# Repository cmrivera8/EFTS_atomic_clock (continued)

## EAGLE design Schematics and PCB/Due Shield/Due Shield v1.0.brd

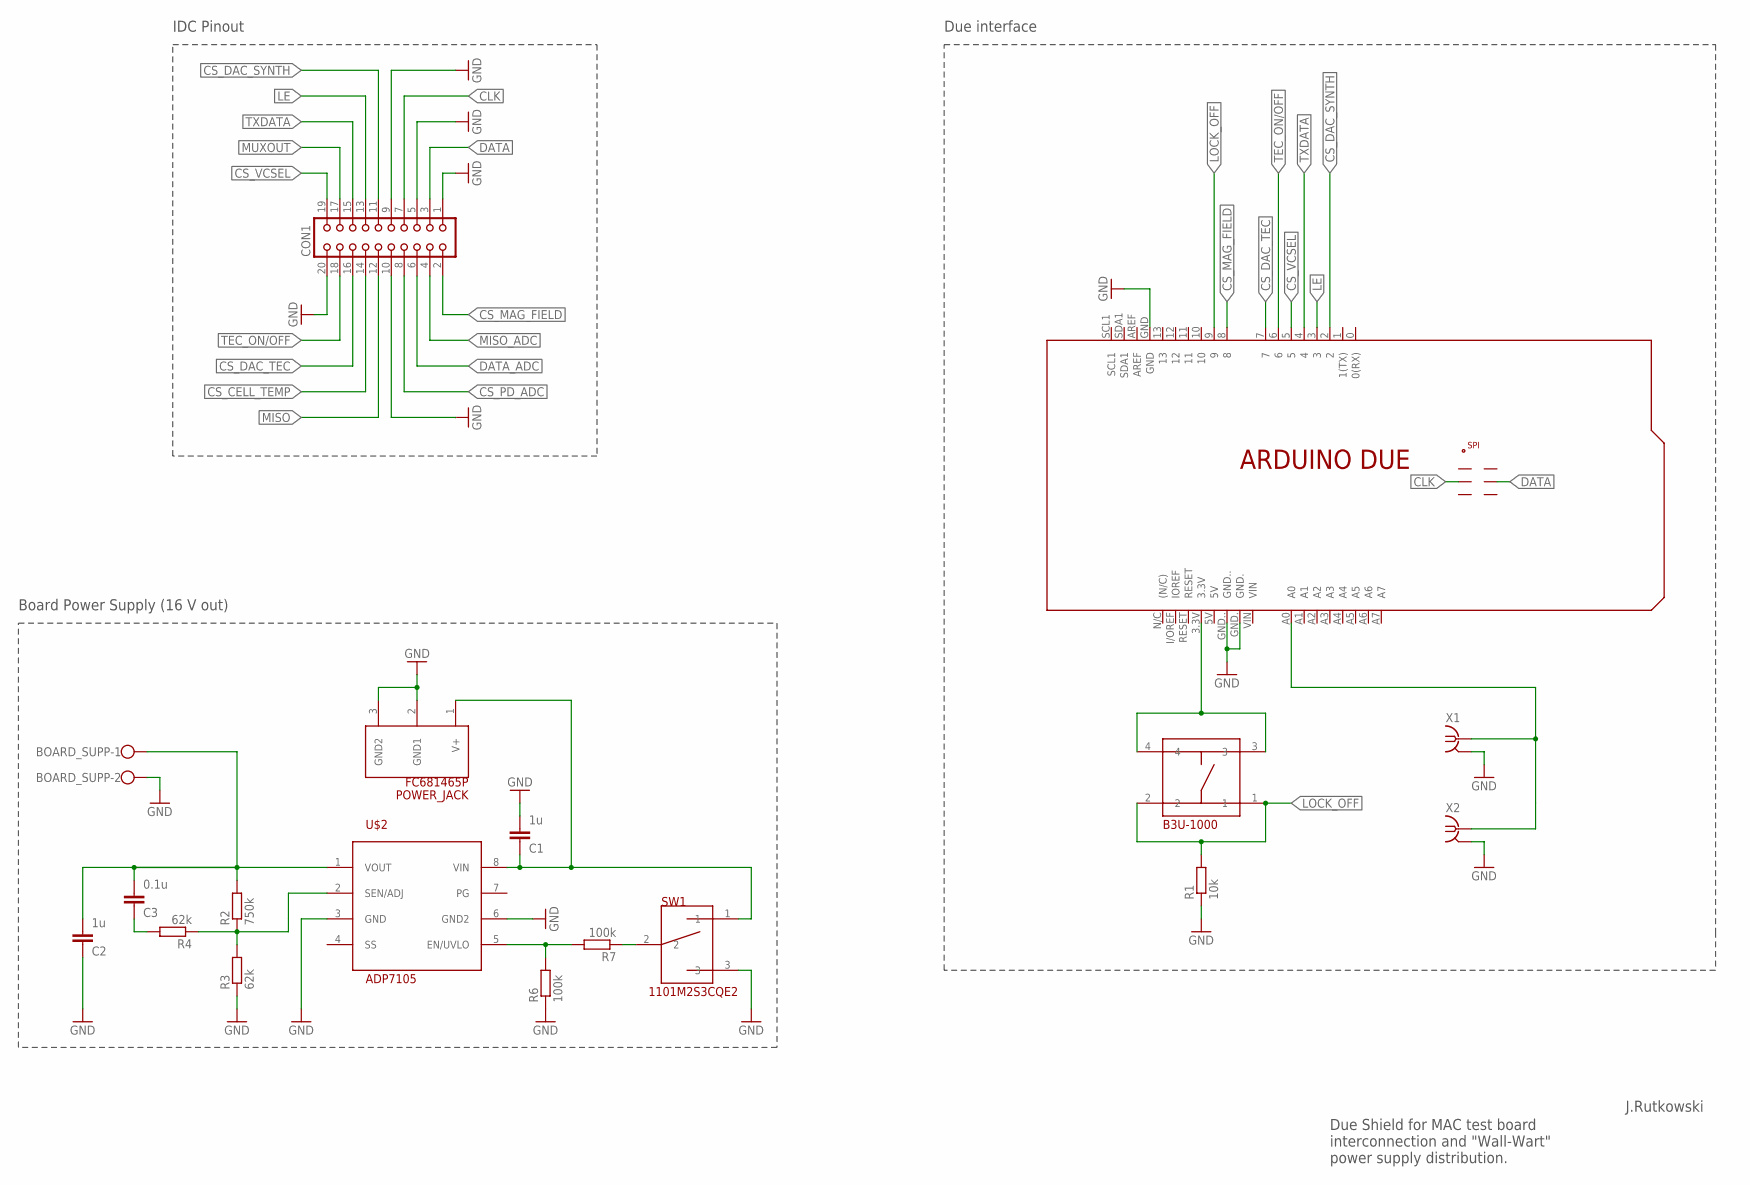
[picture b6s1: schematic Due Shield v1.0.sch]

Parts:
BOARD_SUPP: W237-102
C1, C2: 1u; C0805K
C3: 0.1u; C0805K
CON1: CON20
PCB1: ARDUINO_DUE
POWER_JACK: FC681465P
R1: 10k; R0603
R2: 750k; R0603
R3, R4: 62k; R0603
R6, R7: 100k; R0603
SW1: 1101M2S3CQE2
U$1: B3U-1000
U$2: ADP7105; SO8
X1, X2: BU-SMA-V

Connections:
CLK: CON1.7, PCB1.SCK
CS_CELL_TEMP: CON1.14
CS_DAC_SYNTH: CON1.11, PCB1.2
CS_DAC_TEC: CON1.16, PCB1.7
CS_MAG_FIELD: CON1.2, PCB1.8
CS_PD_ADC: CON1.8
CS_VCSEL: CON1.19, PCB1.5
DATA: CON1.3, PCB1.MOSI
DATA_ADC: CON1.6
GND: BOARD_SUPP.2, C1.1, C2.2, CON1.1, CON1.5, CON1.9, CON1.10, CON1.20, PCB1.GND, PCB1.GND., PCB1.GND.., POWER_JACK.2 (GND1), POWER_JACK.3 (GND2), R1.1, R3.1, R6.1, SW1.3, U$2.3 (GND), U$2.6 (GND2), X1.2, X1.3 (2), X1.4 (2), X1.5 (2), X2.2, X2.3 (2), X2.4 (2), X2.5 (2)
LE: CON1.13, PCB1.3
LOCK_OFF: PCB1.9, R1.2, U$1.1, U$1.2
MISO: CON1.12
MISO_ADC: CON1.4
MUXOUT: CON1.17
unnamed: PCB1.3.3V, U$1.3, U$1.4
unnamed: PCB1.A0, X1.1, X2.1
unnamed: BOARD_SUPP.1, C2.1, C3.1, R2.2, U$2.1 (VOUT)
unnamed: R2.1, R3.2, R4.1, U$2.2 (SEN/ADJ)
unnamed: C1.2, POWER_JACK.1 (V+), SW1.1, U$2.8 (VIN)
unnamed: C3.2, R4.2
unnamed: R6.2, R7.2, U$2.5 (EN/UVLO)
unnamed: R7.1, SW1.2
TEC_ON/OFF: CON1.18, PCB1.6
TXDATA: CON1.15, PCB1.4

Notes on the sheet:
IDC Pinout
Due interface
Board Power Supply (16 V out)
J.Rutkowski
Due Shield for MAC test board interconnection and "Wall-Wart" power supply distribution.

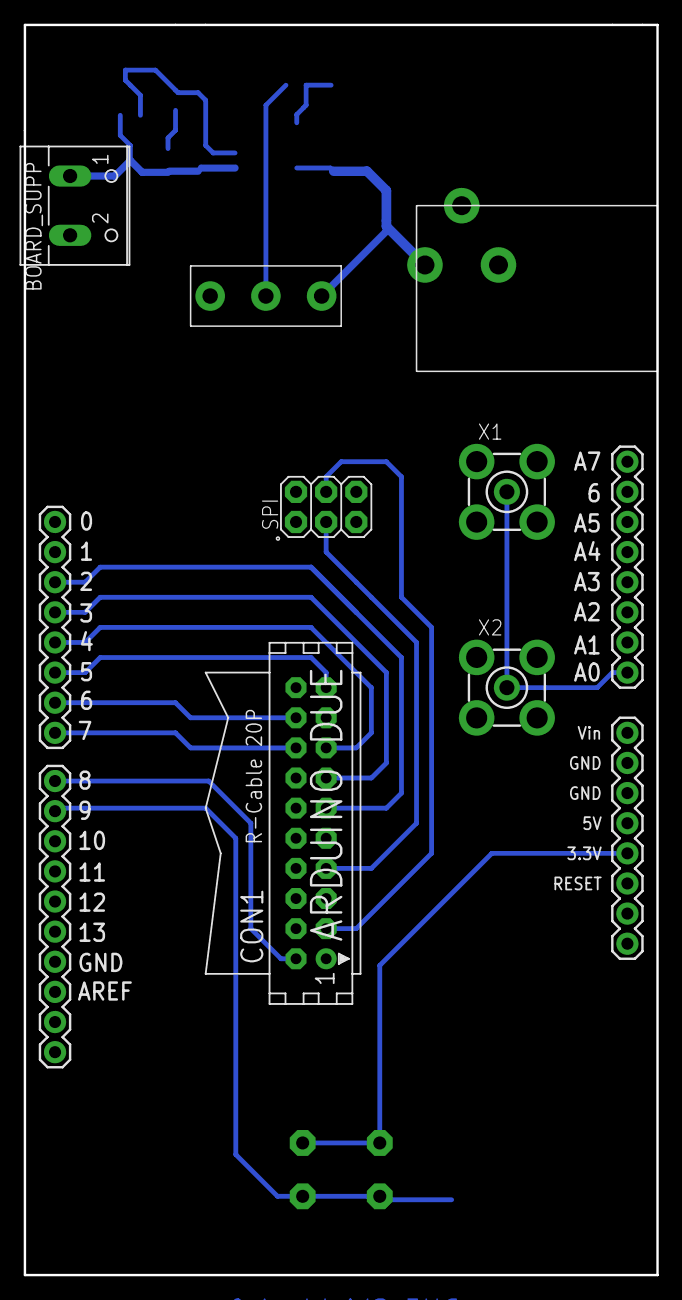
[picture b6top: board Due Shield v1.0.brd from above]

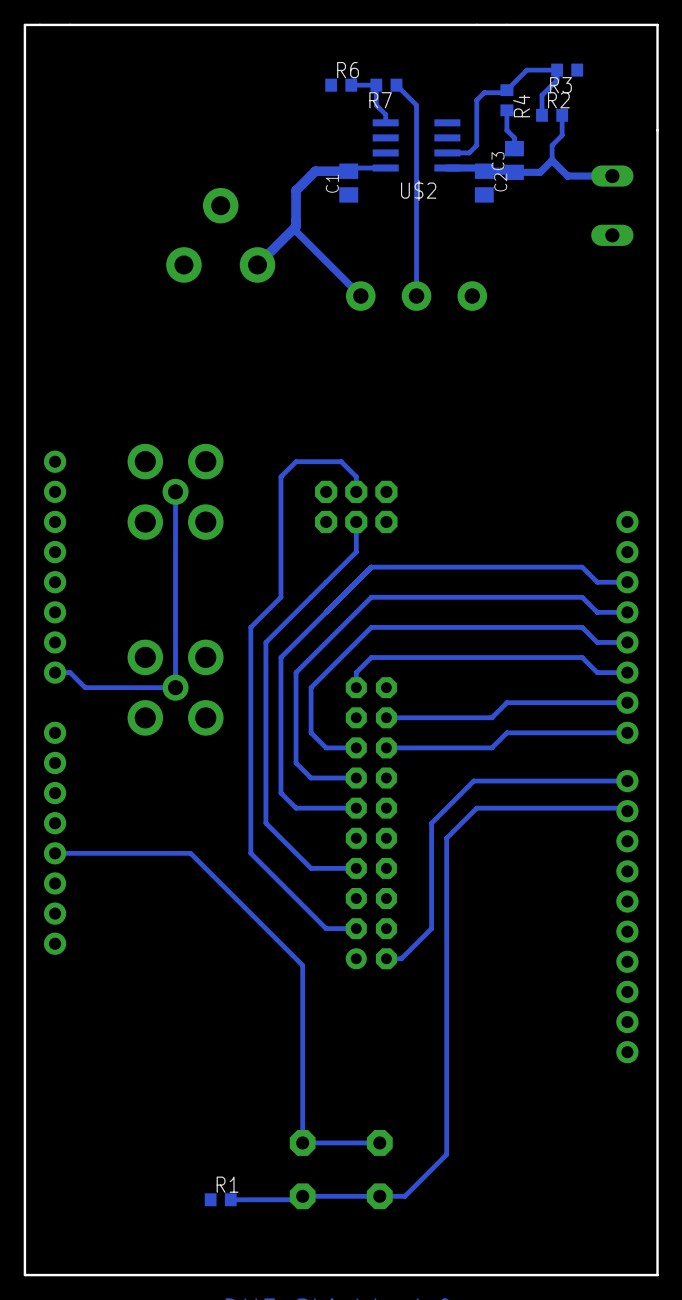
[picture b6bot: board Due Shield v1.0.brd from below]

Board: 2 copper layers, 53.3 x 105.4 mm, 18 parts (10 on the bottom side), 19 nets.

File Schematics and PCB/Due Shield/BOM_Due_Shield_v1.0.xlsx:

Bill of Materials
Assembly Name: | Due Shield
Revision: | 1.0
Date: | 42601
Part Name | Value | Package | Description | Manufacturer | MPN | Ref. Farnell | Quantity | Approx. Unit Price | Stock
C1, C2 | 1u | 0805 | Condensateur céramique multicouche CMS, Série GRM, 1 µF, ± 10%, X7R, 50 V | MURATA | GRM21BR71H105KA12L | 1735541 | 2 | 0.158 | none
C3 | 0.1u | 0805 | Condensateur céramique multicouche CMS, Série GRM, 0.1 µF, ± 10%, X7R, 50 V | MURATA | GRM21BR71H104KA01L | 8820120 | 1 | 0.0874 | none
R1 | 10k | 0603 | Résistance à puce CMS, Céramique, Série MCMR , 10 kohm, 75 V, 100 mW, ± 1% | MULTICOMP | MCMR06X1002FTL | 2073349 | 1 | 0.0142 | ok
R2 | 750k | 0603 | Résistance à puce CMS, Couche mince, Série MCT, 750 kohm, 75 V,100 mW, ± 1% | VISHAY | MCT06030C7503FP500 | 2325290 | 1 | 0.122 | none
R3, R4 | 62k | 0603 | Résistance à puce CMS, Couche épaisse, Série AEC-Q200 CRCW, 62 kohm, 75 V | VISHAY | CRCW060362K0FKEA | 2138478 | 2 | 0.0147 | none
R6, R7 | 100k | 0603 | Résistance à puce CMS, Couche épaisse, Série RC, 100 kohm, 50 V, 100 mW, ± 1% | YAGEO | RC0603FR-13100KL | 2309107 | 2 | 0.0195 | ok
CON1 | - | IDC THT | Connecteur fil-à-carte, Vertical, Série T821, 20 Contact(s), Embase, 2.54 mm | AMPHENOL | T821120A1S100CEU | 2215309 | 1 | 0.533 | ok
BOARD_SUPP | - | THT | Bornier fil-à-carte, 2 Voies, 300 V, 16 A, 26 AWG, 12 AWG | MULTICOMP | MC000048 | 2008019 | 1 | 0.406 | ok
POWER_JACK | - | THT | Connecteur d'alimentation DC, Femelle, 5 A, 2.5 mm | CLIFF ELECTRONIC COMPONENTS | FC681465P | 1854512 | 1 | 1.24 | none
SW1 | - | THT | Commutateur à glissière, Série 1000, SPDT, On-Aucun-On, 6 A, 250 V | C & K COMPONENTS | 1101M2S3CQE2 | 1437697 | 1 | 3.26 | none
U$1 | - | THT | Commutateur tactile, Non lumineux, 1.57 N, 24 V, 50 mA, A souder | OMRON ELECTRONIC COMPONENTS | B3W-1000 | 176986 | 1 | 0.448 | none
X1, X2 | - | THT | Connecteur coaxial / RF, Coaxial SMA, Jack droit, A souder, Laiton | TE CONNECTIVITY / GREENPAR | 1-1478979-0 | 1056377 | 2 | 4.62 | none
U$2 | - | SOIC-8 | Régulateur de tension LDO, Ajustable, 3.3V à 20V in, 350mV drop, 1.22V à 19V/0.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 | ANALOG DEVICES | ADP7105ARDZ | 2361533 | 1 | 3.89 | none

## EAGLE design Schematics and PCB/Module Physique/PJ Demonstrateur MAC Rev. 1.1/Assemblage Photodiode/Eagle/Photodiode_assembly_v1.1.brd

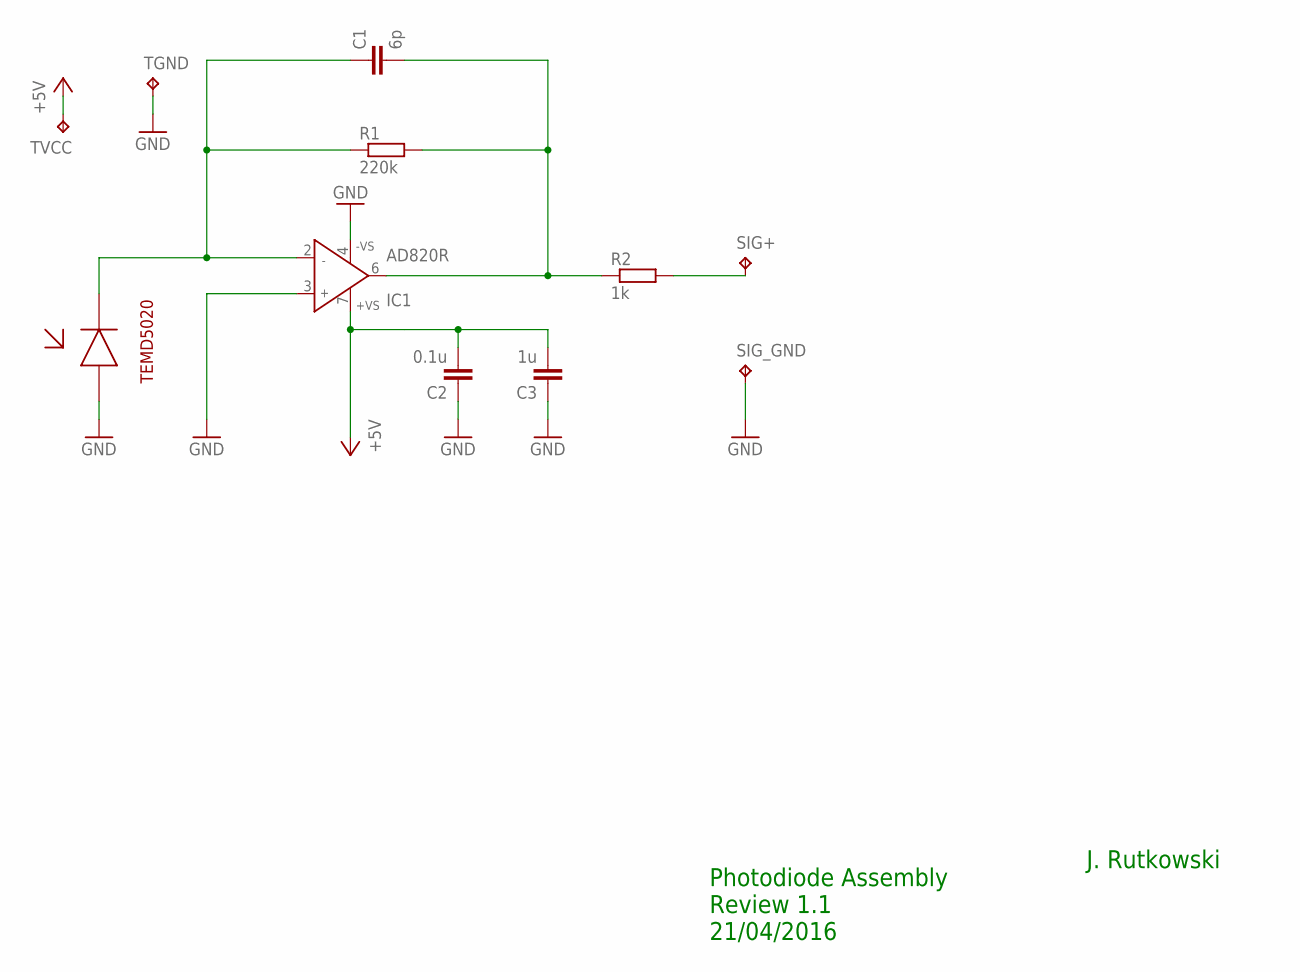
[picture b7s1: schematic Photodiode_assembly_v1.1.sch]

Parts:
C1: 6p; C0805K
C2: 0.1u; C0805K
C3: 1u; C0805K
D1: TEMD5020; TEMD5020_OUTLINE
IC1: AD820R; SO8
R1: 220k; R0805
R2: 1k; R0805
SIG+: TPPAD1-13Y; P1-13Y
SIG_GND: TPPAD1-13Y; P1-13Y
TGND: TPPAD1-13Y; P1-13Y
TVCC: TPPAD1-13Y; P1-13Y

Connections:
+5V: C2.2, C3.2, IC1.7 (+VS), TVCC.TP
GND: C2.1, C3.1, D1.ANODE_BRD (ANODE_SYM), IC1.3 (IN+), IC1.4 (-VS), SIG_GND.TP, TGND.TP
unnamed: C1.1, D1.CATHODE_BRD (CATHODE), IC1.2 (IN-), R1.1
unnamed: C1.2, IC1.6 (OUT), R1.2, R2.1
unnamed: R2.2, SIG+.TP

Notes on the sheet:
Photodiode Assembly Review 1.1 21/04/2016
J. Rutkowski

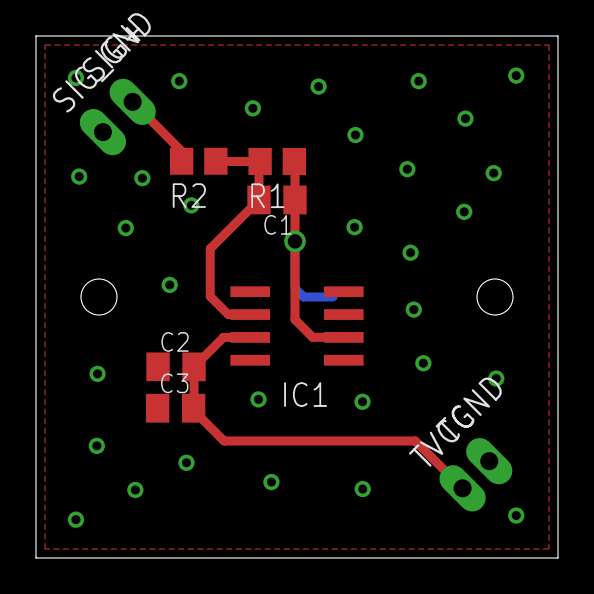
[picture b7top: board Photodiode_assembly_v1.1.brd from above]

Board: 2 copper layers, 29.0 x 29.0 mm, 11 parts (1 on the bottom side), 5 nets.

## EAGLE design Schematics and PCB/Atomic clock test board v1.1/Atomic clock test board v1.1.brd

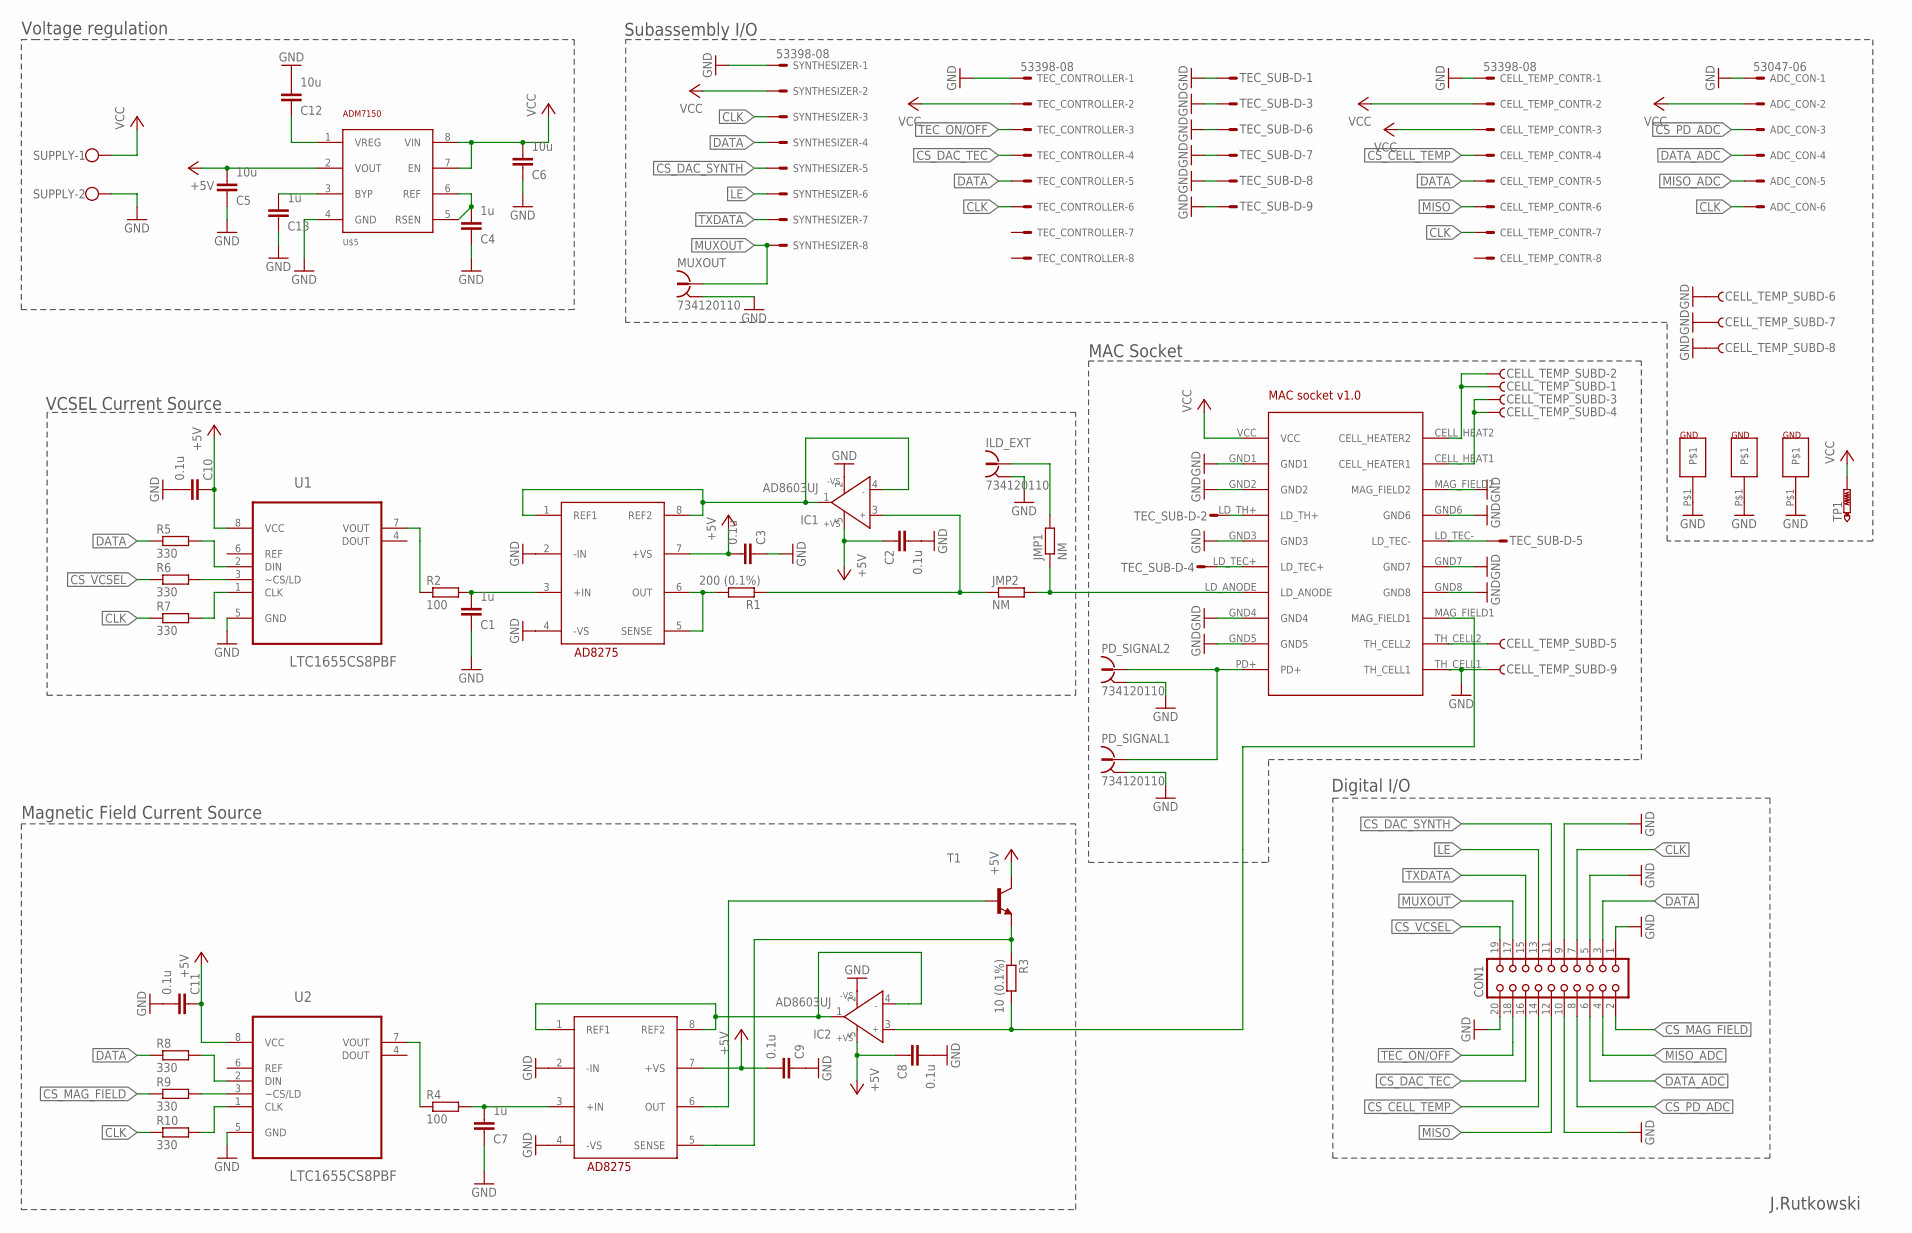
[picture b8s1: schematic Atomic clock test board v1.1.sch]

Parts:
ADC_CON: 53047-06
C1, C4, C7, C13: 1u; C0603K
C2, C3, C8, C9, C10, C11: 0.1u; C0603K
C5, C6, C12: 10u; C0603K
CELL_TEMP_CONTR: 53398-08
CELL_TEMP_SUBD: F09HPS; F09HP
CON1: CON20
IC1, IC2: AD8603UJ; SOT23-5
ILD_EXT: 734120110
JMP1, JMP2: NM; R0402
MUXOUT: 734120110
PD_SIGNAL1, PD_SIGNAL2: 734120110
R1: 200 (0.1%); R0603
R2, R4: 100; R0603
R3: 10 (0.1%); R0603
R5, R6, R7, R8, R9, R10: 330; R0603
SUPPLY: W237-102
SYNTHESIZER: 53398-08
T1: MMBT3904LT1-NPN-SOT23-BEC; SOT23-BEC
TEC_CONTROLLER: 53398-08
TEC_SUB-D: M09HPS; M09HP
TP1: PTR1PAD1-13; P1-13
U1, U2: LTC1655CS8PBF; SOIC127P600X175-8N
U$1: MAC_MOUNT_V1; MAC_MOUNT_PAC_V1
U$2, U$4: AD8275; MSOP08
U$5: ADM7150; SO8
U$6, U$7, U$8: GND_PAD

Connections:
+5V: C2.2, C3.1, C5.1, C8.2, C9.1, C10.2, C11.2, IC1.5 (+VS), IC2.5 (+VS), T1.C, U1.8 (VCC), U2.8 (VCC), U$2.7 (+VS), U$4.7 (+VS), U$5.2 (VOUT)
CLK: ADC_CON.6, CELL_TEMP_CONTR.7, CON1.7, R7.1, R10.1, SYNTHESIZER.3, TEC_CONTROLLER.6
CS_CELL_TEMP: CELL_TEMP_CONTR.4, CON1.14
CS_DAC_SYNTH: CON1.11, SYNTHESIZER.5
CS_DAC_TEC: CON1.16, TEC_CONTROLLER.4
CS_MAG_FIELD: CON1.2, R9.1
CS_PD_ADC: ADC_CON.3, CON1.8
CS_VCSEL: CON1.19, R6.1
DATA: CELL_TEMP_CONTR.5, CON1.3, R5.1, R8.1, SYNTHESIZER.4, TEC_CONTROLLER.5
DATA_ADC: ADC_CON.4, CON1.6
GND: ADC_CON.1, C1.2, C2.1, C3.2, C4.2, C5.2, C6.2, C7.2, C8.1, C9.2, C10.1, C11.1, C12.1, C13.2, CELL_TEMP_CONTR.1, CELL_TEMP_SUBD.6, CELL_TEMP_SUBD.7, CELL_TEMP_SUBD.8, CELL_TEMP_SUBD.9, CON1.1, CON1.5, CON1.9, CON1.10, CON1.20, IC1.2 (-VS), IC2.2 (-VS), ILD_EXT.S@1 (2), ILD_EXT.S@2 (2), ILD_EXT.S@3 (2), MUXOUT.S@1 (2), MUXOUT.S@2 (2), MUXOUT.S@3 (2), PD_SIGNAL1.S@1 (2), PD_SIGNAL1.S@2 (2), PD_SIGNAL1.S@3 (2), PD_SIGNAL2.S@1 (2), PD_SIGNAL2.S@2 (2), PD_SIGNAL2.S@3 (2), SUPPLY.2, SYNTHESIZER.1, TEC_CONTROLLER.1, TEC_SUB-D.1, TEC_SUB-D.3, TEC_SUB-D.6, TEC_SUB-D.7, TEC_SUB-D.8, TEC_SUB-D.9, U1.5 (GND), U2.5 (GND), U$1.GND1, U$1.GND2, U$1.GND3, U$1.GND4, U$1.GND5, U$1.GND6, U$1.GND7, U$1.GND8, U$1.MAG_FIELD2, U$1.TH_CELL1, U$2.2 (-IN), U$2.4 (-VS), U$4.2 (-IN), U$4.4 (-VS), U$5.4 (GND), U$6.P$1, U$7.P$1, U$8.P$1
LE: CON1.13, SYNTHESIZER.6
MISO: CELL_TEMP_CONTR.6, CON1.12
MISO_ADC: ADC_CON.5, CON1.4
MUXOUT: CON1.17, MUXOUT.1, SYNTHESIZER.8
unnamed: C1.1, R2.2, U$2.3 (+IN)
unnamed: R1.2, U$2.5 (SENSE), U$2.6 (OUT)
unnamed: IC1.3 (IN+), JMP2.1, R1.1
unnamed: IC1.1 (OUT), IC1.4 (IN-), U$2.1 (REF1), U$2.8 (REF2)
unnamed: CELL_TEMP_SUBD.1, CELL_TEMP_SUBD.2, U$1.CELL_HEAT2 (CELL_HEATER2)
unnamed: R2.1, U1.7 (VOUT)
unnamed: T1.B, U$4.6 (OUT)
unnamed: R3.1, T1.E, U$4.5 (SENSE)
unnamed: IC2.1 (OUT), IC2.4 (IN-), U$4.1 (REF1), U$4.8 (REF2)
unnamed: C7.1, R4.2, U$4.3 (+IN)
unnamed: R4.1, U2.7 (VOUT)
unnamed: IC2.3 (IN+), R3.2, U$1.MAG_FIELD1
unnamed: R5.2, U1.2 (DIN)
unnamed: R6.2, U1.3 (~CS/LD)
unnamed: R7.2, U1.1 (CLK)
unnamed: R8.2, U2.2 (DIN)
unnamed: R9.2, U2.3 (~CS/LD)
unnamed: R10.2, U2.1 (CLK)
unnamed: PD_SIGNAL1.1, PD_SIGNAL2.1, U$1.PD+
unnamed: TEC_SUB-D.5, U$1.LD_TEC-
unnamed: TEC_SUB-D.4, U$1.LD_TEC+
unnamed: TEC_SUB-D.2, U$1.LD_TH+
unnamed: CELL_TEMP_SUBD.3, CELL_TEMP_SUBD.4, U$1.CELL_HEAT1 (CELL_HEATER1)
unnamed: JMP1.1, JMP2.2, U$1.LD_ANODE
unnamed: CELL_TEMP_SUBD.5, U$1.TH_CELL2
unnamed: ILD_EXT.1, JMP1.2
unnamed: C4.1, U$5.5 (RSEN), U$5.6 (REF)
unnamed: C12.2, U$5.1 (VREG)
unnamed: C13.1, U$5.3 (BYP)
TEC_ON/OFF: CON1.18, TEC_CONTROLLER.3
TXDATA: CON1.15, SYNTHESIZER.7
VCC: ADC_CON.2, C6.1, CELL_TEMP_CONTR.2, CELL_TEMP_CONTR.3, SUPPLY.1, SYNTHESIZER.2, TEC_CONTROLLER.2, TP1.TP, U$1.VCC, U$5.7 (EN), U$5.8 (VIN)

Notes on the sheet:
Digital I/O
Subassembly I/O
Voltage regulation
VCSEL Current Source
Magnetic Field Current Source
MAC Socket
J.Rutkowski

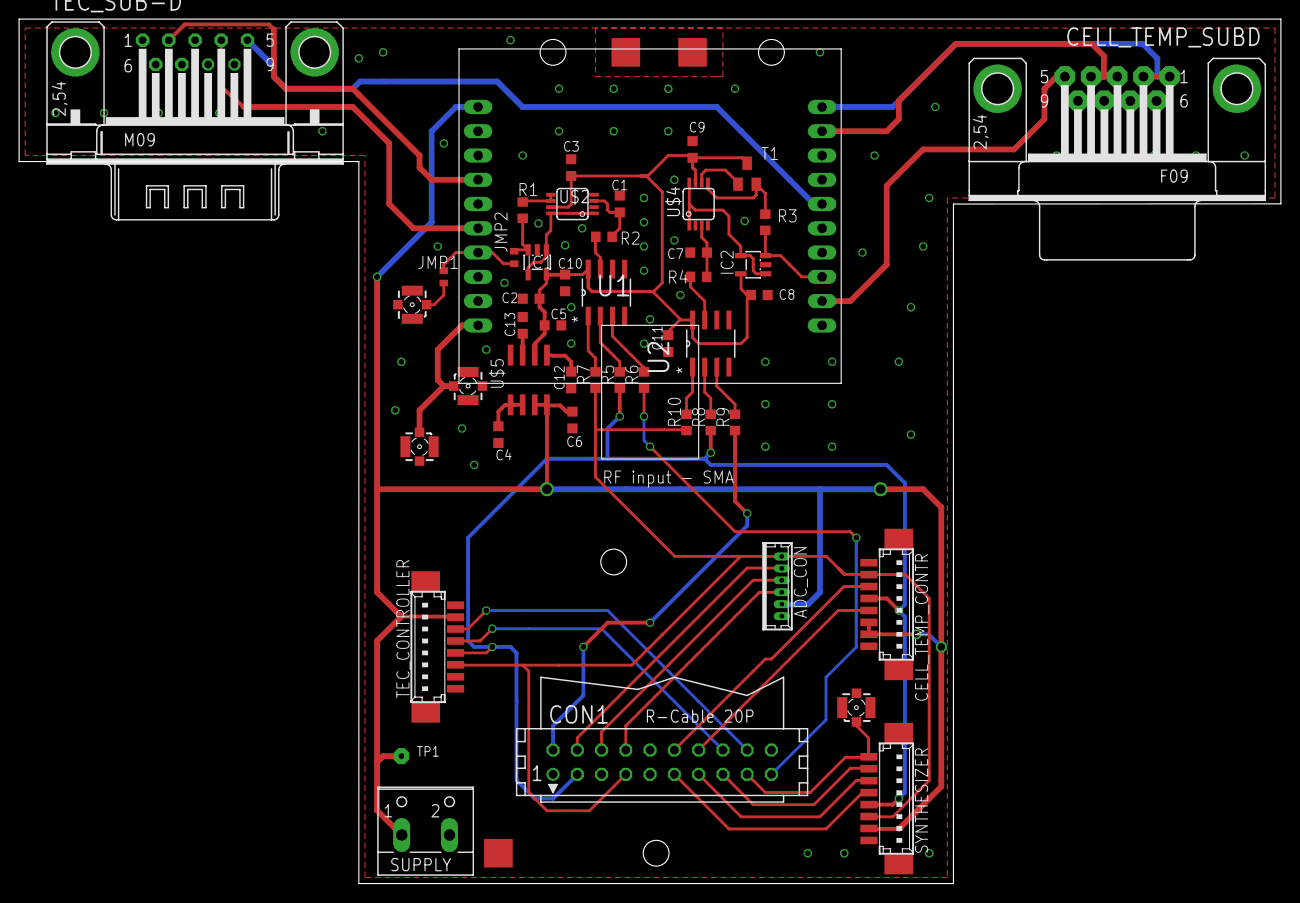
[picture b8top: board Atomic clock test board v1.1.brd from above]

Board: 2 copper layers, 132.1 x 90.5 mm, 50 parts (0 on the bottom side), 47 nets.

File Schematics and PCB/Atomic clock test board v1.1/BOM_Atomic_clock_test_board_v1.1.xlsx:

Bill of Materials
Assembly Name: | Atomic clock test board
Revision: | 1.1
Date: | 42537
Part Name | Value | Package | Description | Manufacturer | MPN | Ref. Farnell | Quantity | Approx. Unit Price | Stock
C1, C4, C7, C13 | 1u | 0603 | Condensateur céramique multicouche CMS, Série GRM, 1 µF, ± 10%, X5R, 6.3 V | MURATA | GRM188R60J105KA01D | 9527699 | 4 | 3.1399999999999997E-2 | ok
C2, C3, C8, C9, C10, C11 | 0.1u | 0603 | Condensateur céramique multicouche CMS, 0.1 µF, ± 10%, X7R, 50 V, 0603 [1608 Me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 | WALSIN | 0603B104K500CT | 2496834 | 6 | 1.26E-2 | ok
C5, C6, C12 | 10 u | 0603 | Condensateur céramique multicouche CMS, Série ZRA, 10 µF, ± 20%, X5R, 25 V | MURATA | ZRB18AR61E106ME01L | 2469398 | 3 | 0.28000000000000003 | none
R1 | 200 | 0603 | Résistance CMS, Couche mince, Série PCF, 200 ohm, 63 mW, ± 0.1%, 50 V | WELWYN | PCF0603R-200RBT1 | 1353134 | 1 | 0.434 | none
R2, R4 | 100 | 0603 | Résistance CMS, Couche mince, Série PCF, 100 ohm, 63 mW, ± 0.1%, 50 V | WELWYN | PCF0603R-100RBT1 | 1160304 | 2 | 0.434 | none
R3 | 10 | 0603 | Résistance CMS, Couche mince, Série WIN, 10 ohm, 100 mW, ± 0.1%, 75 V | WELWYN | WINT0603LF0310R0B | 2428787 | 1 | 0.77300000000000002 | none
R5, R6, R7, R8, R9, R10 | 330 | 0603 | Résistance CMS, Couche épaisse, Série MCWR, 330 ohm, 100 mW, ± 1%, 50 V | MULTICOMP | MCWR06X3300FTL | 2447339 | 6 | 6.7000000000000002E-3 | ok
ADC_CON | - | THT | Connecteur carte-à-carte, Vertical, Série Archer M52, 5 Contact(s), Embase, 1.2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 | HARWIN | M52-5000545 | 1099543 | 1 | 0.54100000000000004 | none
SUPPLY | - | THT | Bornier fil-à-carte, 2 Voies, 300 V, 16 A, 26 AWG, 12 AWG | MULTICOMP | MC000048 | 2008019 | 1 | 0.40600000000000003 | none
SYNTHESIZER, TEC_CONTROLLER, CELL_TEMP_CONTR | - | SMD | Connecteur fil-à-carte, Série PicoBlade 53398, 8 Contact(s), Embase, 1.25 mm | MOLEX | 53398-0871 | 1125371 | 3 | 1.43 | none
CELL_TEMP_SUBD | - | THT | Connecteur Sub D standard, Angle Droit, Série 182, DE, Embase, 9, Corps en acier | NORCOMP | 182-009-213R171 | 2294287 | 1 | 1.79 | ok
TEC_SUB-D | - | THT | Connecteur Sub D standard, Série SD, DE, Mâle, 9, Corps en acier | AMPHENOL | L717SDE09P1ACH4F | 2401240 | 1 | 3.28 | ok
CON1 | - | IDC THT | Connecteur fil-à-carte, Vertical, Série T821, 20 Contact(s), Embase, 2.54 mm | AMPHENOL | T821120A1S100CEU | 2215309 | 1 | 0.53300000000000003 | ok
MUXOUT, PD_SIGNAL, ILD_EXT | - | U.FL | Connecteur coaxial / RF, Coaxial RF, Jack droit, Montage en surface vertical, 5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 | MOLEX | 73412-0110 | 1340200 | 3 | 0.78400000000000003 | none
IC1, IC2 | - | TSOT23-5 | Amplificateur opérationnel, Simple, 400 kHz, 1 amplificateur, 0.1 V/µs, 1.8V à 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 | ANALOG DEVICES | AD8603AUJZ | 1651290 | 2 | 2.0099999999999998 | none
T1 | - | SOT23 | Transistor simple bipolaire (BJT), NPN, 40 V, 300 MHz, 300 mW, 200 mA, 100 hFE | DIODES INC. | MMBT3904-7-F | 1773602 | 1 | 7.2599999999999998E-2 | none
U$2, U$4 | - | MSOP-8 | Amplificateur différentiel, Niveau Adaptateur, 1 Amplificateur(s), 300 µV, 15 M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 | ANALOG DEVICES | AD8275ARMZ | 2094193 | 2 | 3.78 | ok
U$5 | - | SOIC-8 | Régulateur LDO Tension fixe, 4.5V à 16V, 600mV Dropout, 5Vout, 800mAout | ANALOG DEVICES | ADM7150ARDZ-5.0 | 2377358 | 1 | 7.37 | none
U1,U2 | - | SOIC-8 | Convertisseur numérique vers analogique, 16 bit, Série, 2.7V à 5.5V | LINEAR TECHNOLOGY | LTC1655LIS8#PBF | 2294807 | 2 | 17.059999999999999 | none

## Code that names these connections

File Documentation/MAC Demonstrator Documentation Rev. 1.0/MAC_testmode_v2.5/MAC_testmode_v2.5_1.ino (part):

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#include <SPI.h>
const int CS_DAC_quartz = 2;                              // Set CS pins
const int CS_ADF4158 = 3;                                 
const int TXDATA = 4;
const int CS_VCSEL = 5;
const int TEC_on_off = 6;
const int CS_DAC_TEC = 7;
const int CS_mag = 8;
const int ButtonPin = 9;
const int ADC_DRDY = 11;
const int CS_ADC = 12;
const int Lock_trigger = 61;

const int lock_step = 1;                                  // Laser lock step
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void setup() {
  pinMode(CS_ADF4158, OUTPUT);
  pinMode(61, OUTPUT);
  pinMode(TXDATA, OUTPUT);
  pinMode(CS_DAC_quartz, OUTPUT);
  pinMode(CS_DAC_TEC, OUTPUT);
  pinMode(TEC_on_off, OUTPUT);
  pinMode(CS_mag, OUTPUT);
  pinMode(CS_VCSEL, OUTPUT);
  pinMode(CS_ADC, OUTPUT);
  pinMode(ButtonPin, INPUT);
  pinMode(ADC_DRDY, INPUT);
  digitalWrite(TEC_on_off, LOW);                          // Sets CS pins high and others low at startup
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}


void toggle_TXDATA(){                                    // Toggles ADF4158 TXDATA pin
  digitalWrite(TXDATA,(!digitalRead(TXDATA)));
}

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
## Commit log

2022-06-05 Matlab code to determine RFout based on registers
2022-06-05 Added documentation
2022-06-08 Improved documentation on registers
2022-06-08 Added comments on registers and flowchart until #6
2022-06-21 Added Absorption graph and marker functionality
2022-06-21 start of locking frequency marker feature
2022-06-26 Improved interface, new controls, carrier markers
2022-07-04 Upload TP latex files
2022-07-05 mac arduino final version clock 1
2022-07-26 Final status at report v1.0
2022-07-28 Clean up refactor
2022-07-28 Added Quartz frequency offset
2022-07-28 Removed TEC serial prints
2022-07-28 Added python extension to qt_mac file
2022-08-14 Clean up of git content
2022-08-14 Clean up of git
2022-08-14 Clean up git
2022-08-14 New ADC function to stop relying on oscilloscope
2022-08-14 remove old code. already in history
2022-08-14 Screen capture for Readme file
2022-08-14 Added Internship Report M1 (Carlos RIVERA)
2022-08-17 Add Word docs with screenshots and debug process
2022-08-17 Add ADC fix to latex,spell check,code line numbers
2022-08-17 Calculate word_to_volt coefficients for new ADC
2022-08-17 Add new ADC range. No more oscilloscope required
2022-08-17 Add video of operating clock and features
